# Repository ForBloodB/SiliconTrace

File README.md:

# 硅迹开源 (SiliconTrace Open)

> 两个中国大学生，不依赖任何商业软件License，仅凭开源工具和一台电脑，走完从芯片设计到板级验证的完整链路。

---

## 项目愿景

本项目是为了推动开源运动而进行的一个尝试，希望能够通过引入AI这种方式，让IC设计的门槛降低，让学习IC设计的门槛降低，并且也推动开源事业的发展。

我们相信：芯片设计不应该是少数人的特权。借助开源工具链和AI辅助，任何人都可以在一台普通的电脑上，完成从RTL代码到物理版图的完整芯片设计流程。

---

## 项目架构

```mermaid
graph TB
    subgraph 用户界面层
        A[AI 交互控制台<br/>Web 前端]
    end

    subgraph 设计流程层
        B[RTL 设计<br/>Verilog HDL]
        C[Yosys 综合<br/>RTL→门级网表]
        D[LibreLane/OpenROAD 后端<br/>布局布线]
        E[GDSII 输出<br/>物理版图]
        F[KiCad 载板<br/>PCB 设计]
    end

    subgraph 工具链层
        G[Yosys 0.64+]
        H[LibreLane 3.x]
        I[KiCad 7.0+]
        J[SKY130 PDK]
    end

    subgraph 自动化层
        K[Shell 脚本<br/>全流程]
        L[Python 脚本<br/>KiCad 生成]
    end

    A -->|发送命令| B
    B --> C --> D --> E --> F
    A -->|实时日志| G
    A -->|实时日志| H
    A -->|实时日志| I
    K --> B
    L --> F
```

```mermaid
graph LR
    subgraph RTL综合
        R1[读取 Verilog] --> R2[逻辑优化<br/>proc/opt/flatten]
        R2 --> R3[寄存器展开<br/>memory_map]
        R3 --> R4[技术映射<br/>techmap/abc]
        R4 --> R5[输出网表<br/>.v + .json]
    end

    subgraph 后端流程-LibreLane/OpenROAD
        P1[Floorplan] --> P2[Global Placement]
        P2 --> P3[Detailed Placement]
        P3 --> P4[CTS]
        P4 --> P5[Global Routing]
        P5 --> P6[Detailed Routing]
        P6 --> P7[Signoff DRC/LVS]
        P7 --> P8[GDSII 版图输出]
    end

    R5 --> P1
```

---

## 详细目录结构

```
SiliconTrace/
│
├── rtl/                              # RTL 源代码
│   ├── picorv32/                     # PicoRV32 RISC-V 处理器核心
│   │   └── picorv32.v                # Verilog 源码 (3049行)
│   └── serv/                         # SERV 串行 RISC-V 处理器
│
├── synthesis/                        # Yosys 综合
│   ├── synth.ys                      # 综合脚本模板
│   ├── run_synth.sh                  # 综合运行脚本
│   └── constraints/                  # SDC 时序约束
│       ├── picorv32.sdc
│       └── serv_synth_wrapper.sdc
│
├── backend/                          # 后端配置
│   └── config/                       # LibreLane 配置文件
│       └── picorv32_librelane_sky130.yaml  # PicoRV32 配置
│
├── scripts/                          # 自动化脚本
│   ├── run_picorv32_librelane.sh     # PicoRV32 LibreLane 运行脚本
│   ├── run_serv_librelane.sh         # SERV LibreLane 运行脚本
│   └── automation/                   # 全流程脚本
│       ├── run_full_flow.sh          # RTL→GDSII 一键运行
│       └── clean.sh                  # 清理生成文件
│
├── artifacts/                        # 生成输出目录 (gitignored)
│   └── librelane/                    # LibreLane 运行结果
│       ├── picorv32_sky130/          # PicoRV32 设计结果
│       │   └── runs/                 # 运行目录
│       │       └── sky130_picorv32_fullfix13/  # 最佳运行
│       │           └── final/        # 最终输出
│       │               ├── gds/      # GDSII 文件
│       │               ├── kicad/    # KiCad 文件
│       │               └── metrics.json  # 指标报告
│       └── serv_sky130/              # SERV 设计结果
│
├── kicad/                            # KiCad PCB 设计
│   ├── test_board/                   # 测试载板
│   │   ├── test_board.kicad_pro      # 项目文件
│   │   ├── test_board.kicad_sch      # 原理图
│   │   └── test_board.kicad_pcb      # PCB Layout
│   ├── symbols/                      # 原理图符号库
│   └── footprints/                   # 封装库
│
├── frontend/                         # AI 交互控制台
│   ├── app.py                        # Flask 后端
│   └── templates/                    # Web 前端模板
│
├── docker/                           # Docker 环境
│   ├── Dockerfile                    # EDA 工具链镜像
│   └── docker-compose.yml            # Docker Compose 配置
│
├── tests/                            # 测试
│   ├── simulation/                   # 仿真测试
│   └── formal/                       # 形式验证
│
├── docs/                             # 文档
│   └── COMMANDS.md                   # 完整命令手册
│
├── README.md                         # 本文件
├── USAGE.md                          # 使用说明
├── PROGRESS.md                       # 进度记录
└── .gitignore
```

---

## 核心工具链

| 工具 | 用途 | 版本 | 开源协议 |
|------|------|------|----------|
| **Yosys** | RTL 综合 (Verilog → 门级网表) | 0.64+ | ISC |
| **LibreLane** | 开源数字后端流程 (基于 OpenROAD) | 3.x | Apache 2.0 |
| **OpenROAD** | 开源 EDA 平台 (通过 LibreLane 调用) | Latest | BSD |
| **Magic** | 版图编辑和 DRC 检查 | Latest | MIT |
| **KLayout** | 版图查看和 DRC 检查 | Latest | GPL |
| **Netgen** | LVS 网表对比 | Latest | BSD |
| **KiCad** | 开源 PCB 设计 | 7.0+ | GPL |
| **SKY130 PDK** | SkyWater 130nm 工艺设计套件 | sky130A | Apache 2.0 |
| **Volare** | PDK 版本管理工具 | 0.20+ | MIT |

---

## 快速开始

### 方式一：直接构建 (推荐学习)

适合希望深入了解每一步流程的学习者。

#### 1. 系统依赖安装

```bash
# 更新系统
sudo apt update && sudo apt upgrade -y

# 安装基础依赖
sudo apt install -y build-essential cmake git curl wget python3 python3-pip

# 安装 KiCad
sudo apt install -y kicad

# 安装 Python 工具
pip3 install librelane volare
```

#### 2. 安装 Yosys

```bash
# 方法 1: apt 安装 (推荐)
sudo apt install -y yosys

# 方法 2: 源码编译
git clone https://github.com/YosysHQ/yosys.git
cd yosys && make -j$(nproc) && sudo make install
```

#### 3. 安装 SKY130 PDK

```bash
volare enable --pdk sky130
```

#### 4. 运行 PicoRV32 完整流程

```bash
cd ~/SiliconTrace

# 运行 PicoRV32 LibreLane 流程
bash scripts/run_picorv32_librelane.sh sky130_picorv32

# 查看结果
ls artifacts/librelane/picorv32_sky130/runs/sky130_picorv32/final/
```

#### 5. 查看生成的 KiCad 文件

```bash
# 打开 KiCad 项目
kicad artifacts/librelane/picorv32_sky130/runs/sky130_picorv32/final/kicad/PicoRV32_BGA256.kicad_pro
```

#### 6. 使用 AI 交互控制台

```bash
pip3 install flask flask-cors
python3 frontend/app.py
# 浏览器访问: http://localhost:5000
```

---

### 方式二：Docker 构建 (推荐部署)

适合希望快速搭建环境或在多台机器上复现的用户。

#### 1. 安装 Docker

```bash
# 安装 Docker
sudo apt-get update
sudo apt-get install -y ca-certificates curl gnupg lsb-release

# 添加 Docker GPG 密钥和源
sudo mkdir -p /etc/apt/keyrings
curl -fsSL https://download.docker.com/linux/ubuntu/gpg | sudo gpg --dearmor -o /etc/apt/keyrings/docker.gpg
echo "deb [arch=$(dpkg --print-architecture) signed-by=/etc/apt/keyrings/docker.gpg] \
  https://download.docker.com/linux/ubuntu $(lsb_release -cs) stable" | \
  sudo tee /etc/apt/sources.list.d/docker.list > /dev/null

# 安装 Docker Engine
sudo apt-get update
sudo apt-get install -y docker-ce docker-ce-cli containerd.io docker-compose-plugin

# 将用户添加到 docker 组
sudo usermod -aG docker $USER
newgrp docker
```

#### 2. 构建 Docker 镜像

```bash
cd ~/SiliconTrace

# 构建包含所有 EDA 工具的镜像
docker compose -f docker/docker-compose.yml build
```

#### 3. 启动环境

```bash
# 启动 EDA 环境 + AI 前端
docker compose -f docker/docker-compose.yml up -d

# 进入 EDA 容器
docker exec -it silicontrace-eda bash

# 在容器内运行 PicoRV32
bash scripts/run_picorv32_librelane.sh sky130_picorv32
```

---

## AI 交互控制台

硅迹开源提供了一个 Web 界面，让您可以通过交互式命令控制整个设计流程。

### 功能特性

- **流程可视化**: 实时显示 7 个设计步骤的状态 (综合 → Floorplan → Placement → CTS → Routing → STA → GDSII)
- **工具链检测**: 自动检测 Yosys、iEDA、KiCad、PDK 等工具的安装状态
- **实时日志**: 查看每一步的详细执行日志
- **设计切换**: 支持多个 RTL 设计之间的切换和管理
- **文件导入**: 支持导入自定义 RTL 设计、芯片封装、原理图符号
- **生成文件浏览**: 直接在前端查看后端生成的网表、DEF、GDSII 等文件
- **MCP 接口**: 提供程序化上传 API，支持 AI 代理调用

### 启动方式

```bash
pip3 install flask flask-cors
python3 frontend/app.py
```

浏览器访问: http://localhost:5000

### 可用命令

| 命令 | 说明 |
|------|------|
| `综合` / `synthesis` / `yosys` | 运行 Yosys 综合 |
| `floorplan` / `fp` / `布局规划` | 运行 Floorplan |
| `placement` / `pl` / `布局` | 运行 Placement |
| `cts` / `时钟树` | 运行 CTS |
| `routing` / `rt` / `布线` | 运行 Routing |
| `sta` / `时序分析` | 运行 STA |
| `gdsii` / `gds` | 生成 GDSII |
| `全流程` / `full flow` | 运行完整 RTL→GDSII 流程 |
| `status` / `状态` | 查看项目状态 |

### MCP 上传接口

```bash
# RTL 设计上传
curl -X POST http://localhost:5000/api/upload/mcp \
  -H "Content-Type: application/json" \
  -d '{
    "action": "import",
    "type": "rtl",
    "filename": "my_design.v",
    "content": "module my_design(...); endmodule",
    "encoding": "text",
    "design_name": "my_design"
  }'

# 芯片封装上传
curl -X POST http://localhost:5000/api/upload/mcp \
  -H "Content-Type: application/json" \
  -d '{
    "action": "import",
    "type": "footprint",
    "filename": "my_chip.kicad_mod",
    "content": "(module my_chip ...)",
    "encoding": "text"
  }'
```

---

## 输出文件说明

| 阶段 | 输出文件 | 查看方式 |
|------|----------|----------|
| 综合 | `artifacts/synthesis/picorv32_netlist.v` | Vim / VS Code |
| GDSII | `artifacts/librelane/picorv32_sky130/runs/*/final/gds/` | KLayout |
| DRC 报告 | `artifacts/librelane/picorv32_sky130/runs/*/final/metrics.json` | Vim / VS Code |
| KiCad PCB | `artifacts/librelane/picorv32_sky130/runs/*/final/kicad/PicoRV32_BGA256.kicad_pcb` | KiCad |
| KiCad 原理图 | `artifacts/librelane/picorv32_sky130/runs/*/final/kicad/PicoRV32_BGA256.kicad_sch` | KiCad |
| 渲染图 | `artifacts/librelane/picorv32_sky130/runs/*/final/render/` | 图片查看器 |

---

## 设计案例

### PicoRV32 RISC-V 处理器核心

- **工艺**: SKY130 130nm
- **设计规模**: ~3000 行 Verilog
- **Die 面积**: 1200μm × 1200μm
- **标准单元库**: sky130_fd_sc_hd (高密度)
- **封装**: BGA-256 (17mm × 17mm, 1.0mm pitch)
- **Signoff 状态**: DRC=0, LVS=0, XOR=0

### SERV 串行 RISC-V 处理器核心

- **工艺**: SKY130 130nm
- **设计规模**: 极小 (串行架构)
- **Die 面积**: 600μm × 600μm
- **标准单元库**: sky130_fd_sc_hd (高密度)
- **Signoff 状态**: DRC=0, LVS=0, XOR=0

---

## 参与贡献

欢迎提交 Issue 和 Pull Request！

### 贡献指南

1. Fork 本仓库
2. 创建特性分支 (`git checkout -b feature/AmazingFeature`)
3. 提交更改 (`git commit -m 'Add some AmazingFeature'`)
4. 推送到分支 (`git push origin feature/AmazingFeature`)
5. 创建 Pull Request

---

## 开源协议

本项目采用 [MIT License](LICENSE) 开源协议。

---

## 致谢

- [YosysHQ](https://github.com/YosysHQ) - 开源综合工具
- [LibreLane](https://github.com/efabless/librelane) - 开源数字后端流程
- [OpenROAD](https://github.com/The-OpenROAD-Project/OpenROAD) - 开源 EDA 平台
- [KiCad](https://www.kicad.org/) - 开源 PCB 设计工具
- [SkyWater PDK](https://github.com/google/skywater-pdk) - 130nm 工艺设计套件
- [PicoRV32](https://github.com/cliffordwolf/picorv32) - RISC-V 处理器核心
- [SERV](https://github.com/olofk/serv) - 串行 RISC-V 处理器核心

---

## 联系方式

- GitHub: [SiliconTrace_Open](https://github.com/ForBloodB/SiliconTrace_Open)
- B站: 血舞蝶ForBloodB

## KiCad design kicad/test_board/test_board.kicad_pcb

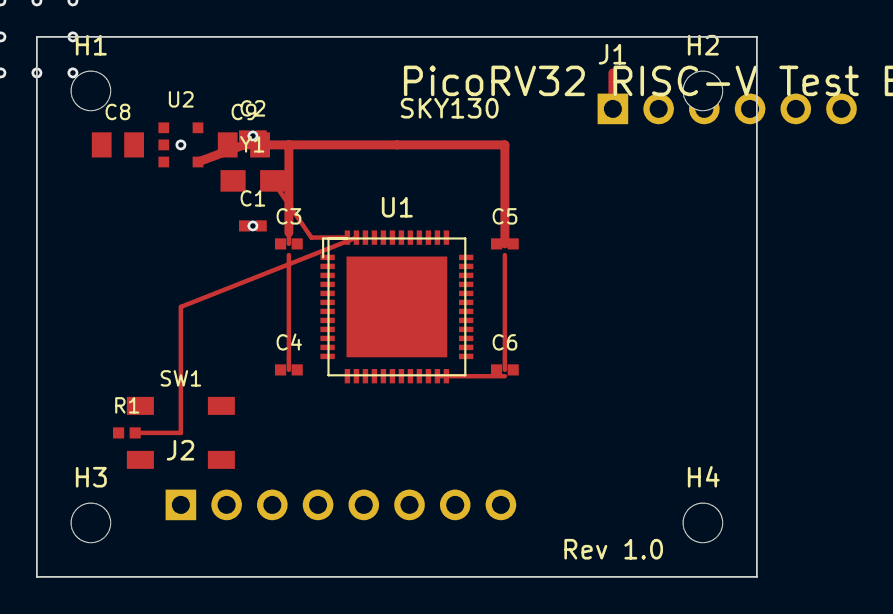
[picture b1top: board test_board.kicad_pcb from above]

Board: 4 copper layers, 40.0 x 30.0 mm, 19 parts (0 on the bottom side), 5 nets.

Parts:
C1, C2: 18pF; C_0402_1005Metric
C3, C4, C5: 100nF; C_0402_1005Metric
C6: 10uF; C_0402_1005Metric
C8, C9: 10uF; C_0805_2012Metric
H1, H2, H3, H4: MountingHole; MountingHole_2.2mm_M2
J1: JTAG; PinHeader_1x06_P2.54mm_Vertical
J2: GPIO; PinHeader_1x08_P2.54mm_Vertical
R1: 10k; R_0402_1005Metric
SW1: RESET; SW_SPST_TL3342
U1: PicoRV32; QFN-48_7x7mm_P0.5mm
U2: LDO_3V3; SOT-23-5
Y1: 100MHz; Crystal_SMD_3215-2Pin_3.2x1.5mm

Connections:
+3V3: C3.1, C4.1, C5.1, C6.1, C9.1, J1.1, R1.1, U1.26, U2.4
CLK: C1.1, C2.1, U1.1, Y1.1
GND: C1.2, C2.2, C3.2, C4.2, C5.2, C6.2, C8.2, C9.2, J1.2, SW1.2, SW1.4, U1.0, U1.25, U2.2, Y1.2
RESETN: R1.2, SW1.1, SW1.3, U1.2
VIN: C8.1, U2.1

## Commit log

2026-04-29 init: 硅迹开源项目初始化
    硅迹开源 (SiliconTrace Open) - 全开源数字IC设计工作室
    项目内容：
    - PicoRV32 RISC-V 核心 RTL 源码 (rv32i)
    - Yosys 综合脚本 + SKY130 HD 标准单元库映射
    - iEDA 后端流程脚本 (Floorplan/Placement/CTS/Routing/STA)
    - 网表转换工具 (Yosys JSON → iEDA Tcl)
2026-04-29 docs: 更新进度总结，记录已完成功能
    - Yosys 综合已验证通过
    - iEDA 后端 FP/PL/CTS 已验证通过
    - KiCad 测试载板设计完成（符号/封装/原理图/PCB）
    - 文档教程和博客已创建
    - 仿真测试和形式验证已创建
    - Git 仓库已初始化
2026-04-29 feat: 完善 KiCad 测试载板四层 PCB 设计
    - 更新 PCB 为 KiCad 7 格式
    - 添加四层板叠层定义 (FR4, ENIG)
    - 完善 QFN-48 封装和热过孔
    - 添加完整的网络连接和布线
2026-04-30 ADD front WEB
2026-04-30 chore: ignore KiCad local history
2026-04-30 test: kicad文件
2026-04-30 test: kicad的pcb文件
2026-04-30 test: wsl connect github
2026-05-01 将生成的文件统一放到同一个文件夹下
2026-05-02 增加示例，完善流程
2026-05-04 用openroad，picorv32的DRC降低为0
2026-05-05 openroad工具
2026-05-10 WORKFOLW web
2026-05-10 Remove local automation and GitHub workflow tracking
